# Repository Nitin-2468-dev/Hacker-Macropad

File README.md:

# Hacker Macropad

A small and compact 3×4 programmable Macropad built around the Seeed XIAO RP2040, running on QMK firmware. Designed for programmers, terminal users, and automation — with layers for navigation, symbols, and macros.

---

## Overall Hackpad

---

## Schematic

* 3×4 key matrix (12 keys)
* 1 diode per key (1N4148)
* ROW2COL diode direction
* Connected to XIAO RP2040 GPIO matrix

---

## PCB Layout

* Custom matrix routing
* Through-hole tactile switches
* XIAO RP2040 footprint
* OLED header with a  rotary encoder footprint
* Compact square layout

---

## Case & Assembly

* Two-piece enclosure
* Top plate with switch cutouts
* Bottom shell holds PCB & XIAO and other componets.
* Corner screw mounting
* Internal clearance for OLED + encoder

---

## Features

* 12 programmable keys (QMK)
* RP2040 native USB
* Multi-layer support
* Coding symbol layer
* Dev / terminal macro layer
* NKRO enabled
* Mouse key support (optional)
* Reset-to-bootloader key
* OLED + Encoder ready (optional)

---

# Bill of Materials (BOM)

| Item                        | Qty | Notes            |
| --------------------------- | --- | ---------------- |
| Seeed XIAO RP2040           | 1   | Main controller  |
| Tactile / Mechanical Switch | 12  | Key switches     |
| 1N4148 Diodes               | 12  | Matrix isolation |
| Custom PCB                  | 1   | design PCB       |
| OLED Display (0.91"/0.96")  | 1   | animation        |
| Rotary Encoder              | 1   | volume knob      |
| M2 / M2.5 Screws            | 4   | Case mounting    |
| Standoffs                   | 4   | PCB mounting     |
| Case (3D Printed)           | 1   | Top + Bottom     |

---

## Default Keymap (Programmer Layout)

### Mode 1 — Navigation

* Arrow keys
* ESC / TAB / HOME / END
* Modifier keys

### Mode 2 — Coding Symbols

`{ } [ ] ( ) | \ < >`

### Mode 3 — Dev Shortcuts

* Ctrl+C / Ctrl+V / Ctrl+Z
* Ctrl+S / Ctrl+F / Ctrl+R
* Alt+Tab
* Reset to bootloader

---

## Firmware

Built using QMK Firmware

### Compile

```bash
qmk clean
qmk compile -kb hacker_macropad -km default
```

---

### Flash (RP2040)

1. Double-tap RESET on XIAO RP2040
2. USB drive appears
3. Copy .uf2 firmware file
4. Done 🎉

---

## About

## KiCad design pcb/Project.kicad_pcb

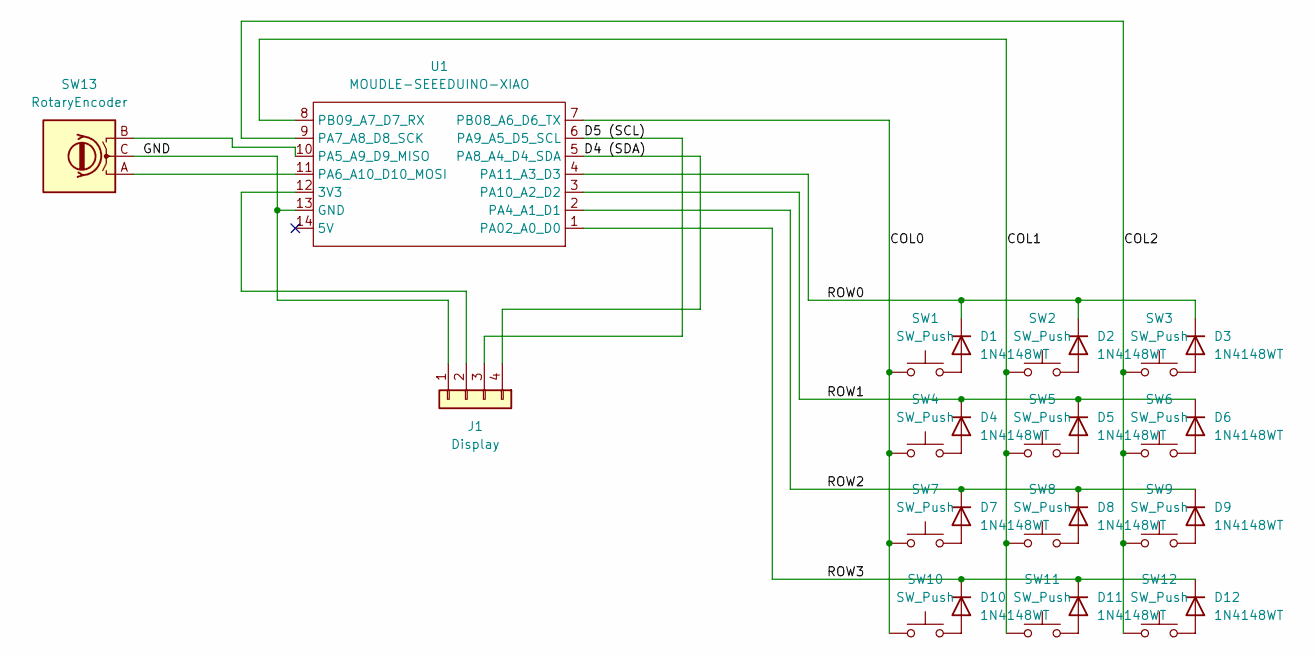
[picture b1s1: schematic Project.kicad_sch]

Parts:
D1, D2, D3, D4, D5, D6, D7, D8, D9, D10, D11, D12: 1N4148WT; D_DO-35_SOD27_P7.62mm_Horizontal
J1: Display; SSD1306-0.91-OLED-4pin-128x32
SW1, SW2, SW3, SW4, SW5, SW6, SW7, SW8, SW9, SW10, SW11, SW12: SW_Push; SW_Cherry_MX_1.00u_PCB
SW13: RotaryEncoder; RotaryEncoder_Alps_EC11E-Switch_Vertical_H20mm
U1: MOUDLE-SEEEDUINO-XIAO; XIAO-Generic-Hybrid-14P-2.54-21X17.8MM

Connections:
/COL0: SW1.1, SW4.1, SW7.1, SW10.1, U1.7 (PB08_A6_D6_TX)
/COL1: SW2.1, SW5.1, SW8.1, SW11.1, U1.8 (PB09_A7_D7_RX)
/COL2: SW3.1, SW6.1, SW9.1, SW12.1, U1.9 (PA7_A8_D8_SCK)
/D4 (SDA): J1.4 (SDA), U1.5 (PA8_A4_D4_SDA)
/D5 (SCL): J1.3 (SCL), U1.6 (PA9_A5_D5_SCL)
/GND: J1.1 (GND), SW13.C, U1.13 (GND)
/ROW0: D1.1 (K), D2.1 (K), D3.1 (K), U1.4 (PA11_A3_D3)
/ROW1: D4.1 (K), D5.1 (K), D6.1 (K), U1.3 (PA10_A2_D2)
/ROW2: D7.1 (K), D8.1 (K), D9.1 (K), U1.2 (PA4_A1_D1)
/ROW3: D10.1 (K), D11.1 (K), D12.1 (K), U1.1 (PA02_A0_D0)
unnamed: D1.2 (A), SW1.2
unnamed: D2.2 (A), SW2.2
unnamed: D3.2 (A), SW3.2
unnamed: D4.2 (A), SW4.2
unnamed: D5.2 (A), SW5.2
unnamed: D6.2 (A), SW6.2
unnamed: D7.2 (A), SW7.2
unnamed: D8.2 (A), SW8.2
unnamed: D9.2 (A), SW9.2
unnamed: D10.2 (A), SW10.2
unnamed: D11.2 (A), SW11.2
unnamed: D12.2 (A), SW12.2
unnamed: J1.2 (VCC), U1.12 (3V3)
unnamed: SW13.B, U1.10 (PA5_A9_D9_MISO)
unnamed: SW13.A, U1.11 (PA6_A10_D10_MOSI)

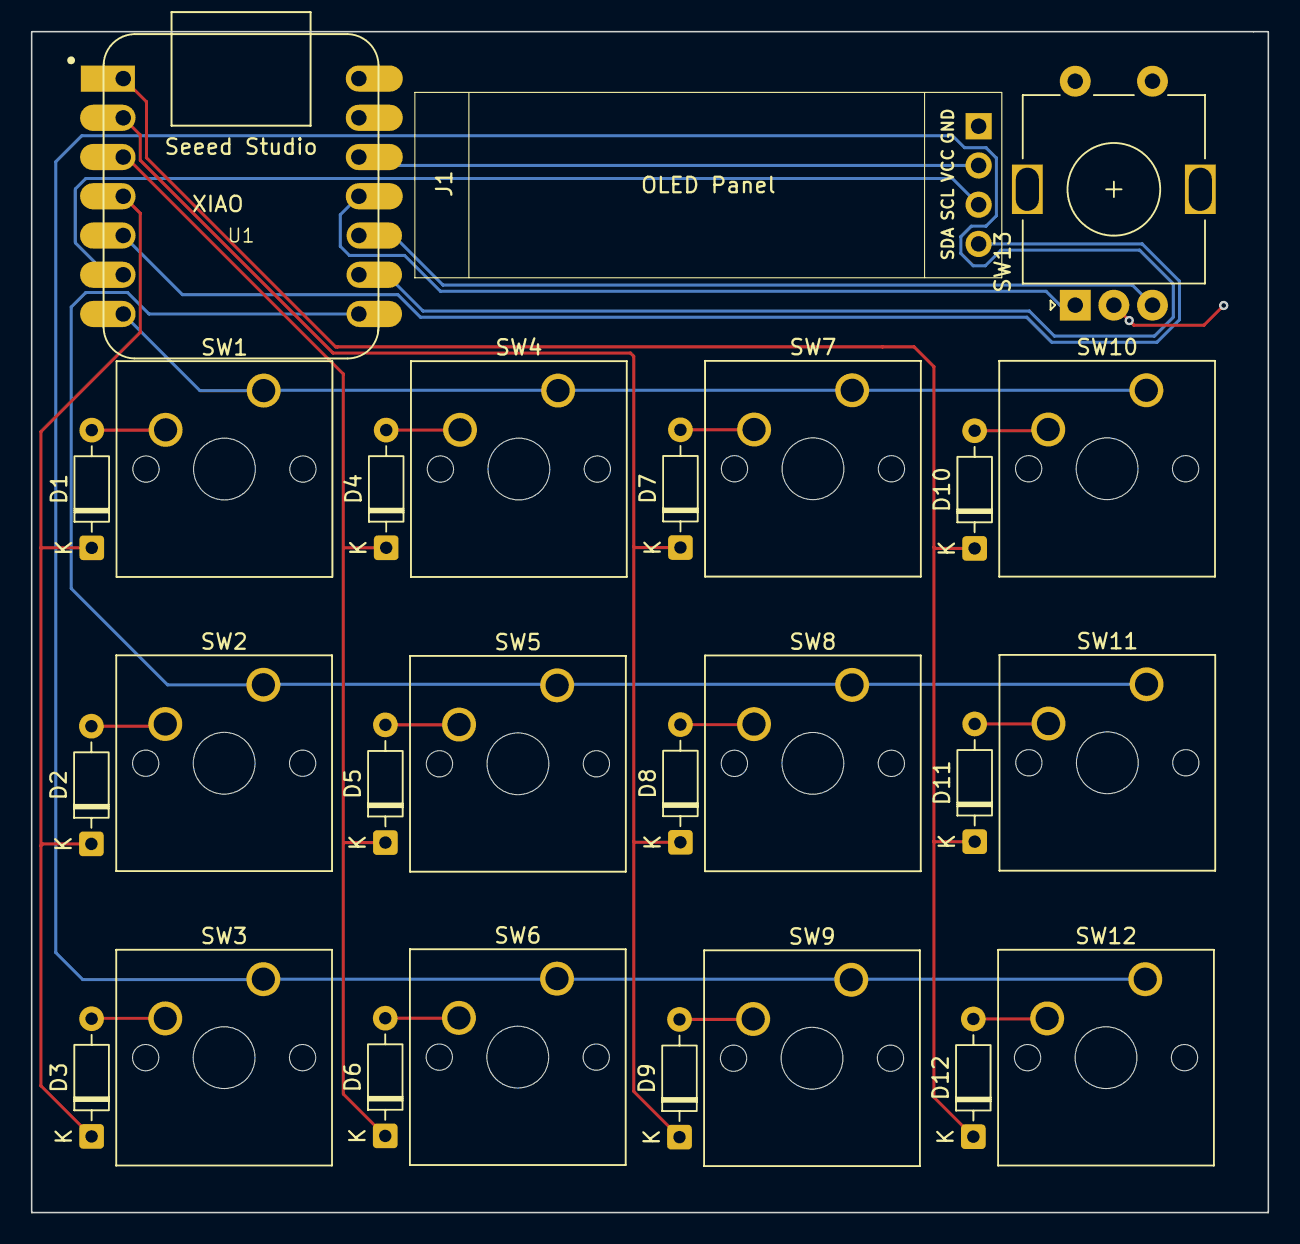
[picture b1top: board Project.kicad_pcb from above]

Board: 2 copper layers, 80.1 x 76.5 mm, 27 parts (0 on the bottom side), 25 nets.

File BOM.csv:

"Id";"Designator";"Footprint";"Quantity";"Designation";"Supplier and ref";
1;"SW5,SW2,SW9,SW10,SW3,SW8,SW4,SW12,SW11,SW7,SW6,SW1";"SW_Cherry_MX_1.00u_PCB";12;"SW_Push";;;
2;"D11,D6,D7,D9,D8,D4,D3,D1,D10,D2,D5,D12";"D_SOD-523";12;"1N4148WT";;;
3;"J1";"SSD1306-0.91-OLED-4pin-128x32";1;"Display";;;
4;"U1";"XIAO-Generic-Hybrid-14P-2.54-21X17.8MM";1;"MOUDLE-SEEEDUINO-XIAO";;;
5;"SW13";"RotaryEncoder_Alps_EC11E-Switch_Vertical_H20mm";1;"RotaryEncoder";;;

"Id";"Designator";"Footprint";"Quantity";"Designation";"Supplier and ref";
1;"SW5,SW2,SW9,SW10,SW3,SW8,SW4,SW12,SW11,SW7,SW6,SW1";"SW_Cherry_MX_1.00u_PCB";12;"SW_Push";;;
2;"D11,D6,D7,D9,D8,D4,D3,D1,D10,D2,D5,D12";"D_SOD-523";12;"1N4148WT";;;
3;"J1";"SSD1306-0.91-OLED-4pin-128x32";1;"Display";;;
4;"U1";"XIAO-Generic-Hybrid-14P-2.54-21X17.8MM";1;"MOUDLE-SEEEDUINO-XIAO";;;
5;"SW13";"RotaryEncoder_Alps_EC11E-Switch_Vertical_H20mm";1;"RotaryEncoder";;;

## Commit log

2026-02-22 inti
2026-02-25 Updating
2026-02-25 README
2026-02-26 The Pain
2026-03-03 Update README.md with additional details
